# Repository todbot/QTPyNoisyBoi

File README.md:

# QTPyNoisyBoi

## QTPy/XIAO-based noisy 3-channel CV modulator Eurorack synth module

This is a bad idea.

It has:
- 3 CV outputs
- 1 gate input
- 3 knobs (next to outputs)
- 3 Neopixels (next to outputs)
- 2 tap buttons
- 1 neopixel on QT Py

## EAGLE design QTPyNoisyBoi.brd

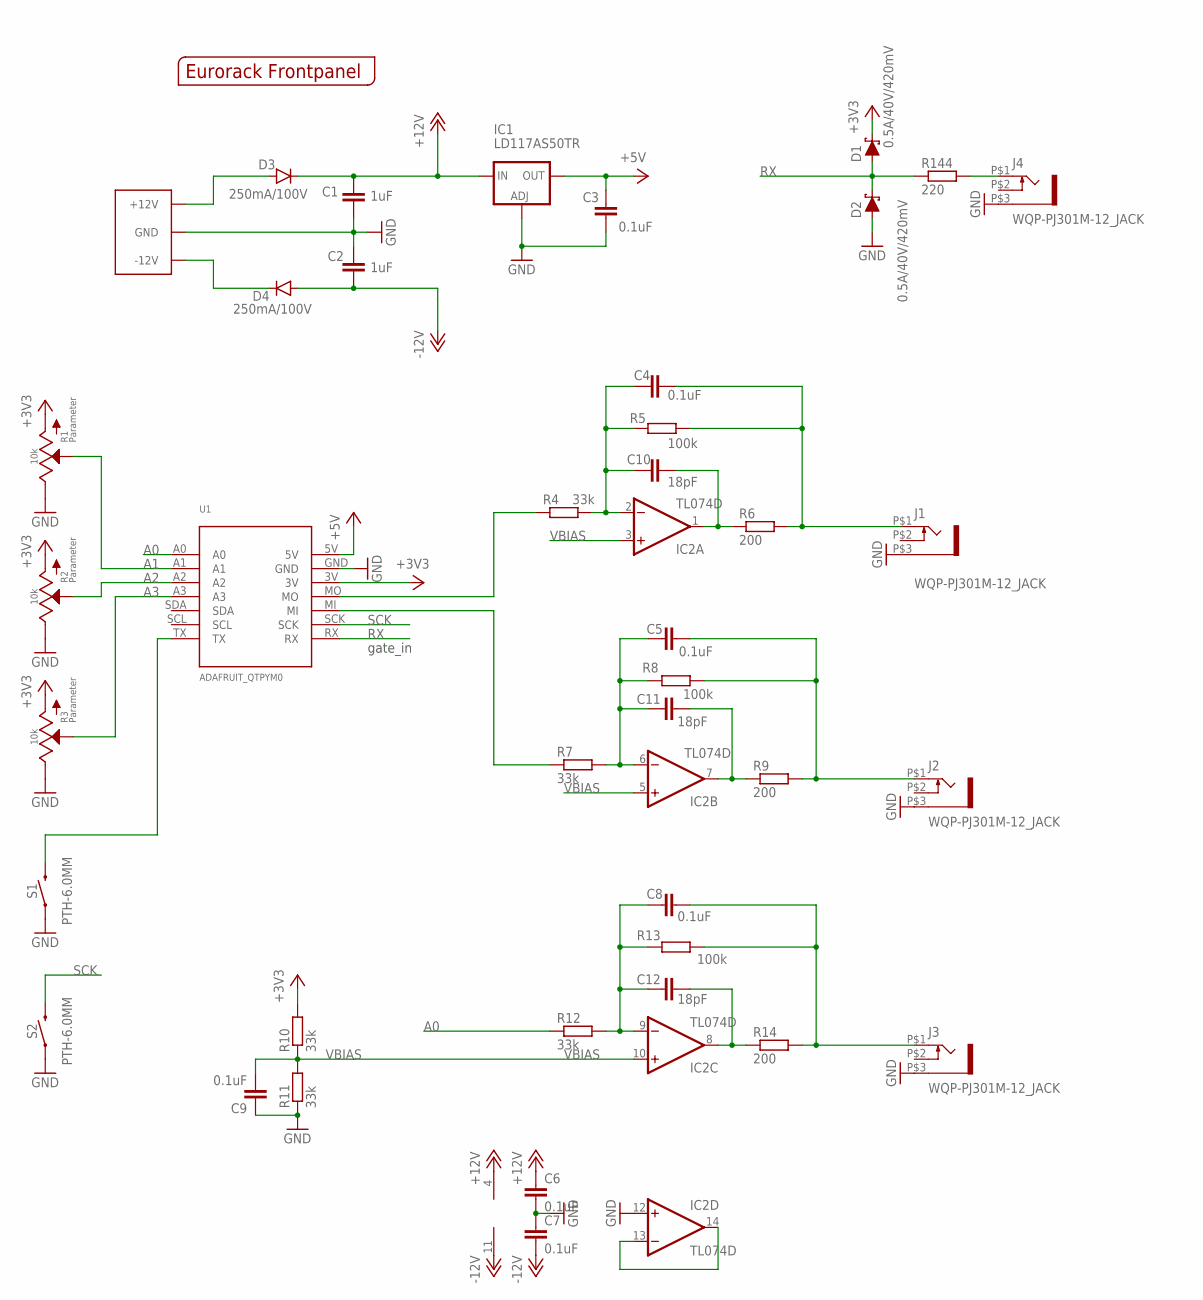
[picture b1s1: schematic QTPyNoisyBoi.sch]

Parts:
C1, C2: 1uF; C0805
C3, C4, C5, C6, C7, C8, C9: 0.1uF; C0805
C10, C11, C12: 18pF; C0805
D1, D2: 0.5A/40V/420mV; SOD-323
D3, D4: 250mA/100V; SOD-323
DIM1: EURO_POWER_LOCKSKINNY; EURO_POWER_HEADER
IC1: LD117AS50TR; SOT223
IC2: TL074D; SO14
J1, J2, J3, J4: WQP-PJ301M-12_JACK
R1, R2, R3: 10k; OG-POTS_ALPS_POT_VERTICAL
R4, R7, R10, R11, R12: 33k; R0805
R5, R8, R13: 100k; R0805
R6, R9, R14: 200; R0805
R144: 220; R0805
S1, S2: PTH-6.0MM; TACTILE_SWITCH_PTH_6.0MM
U1: ADAFRUIT_QTPYM0; ADAFRUIT_QTPY_M0
U$1: EURORACK_PANEL6HP; EURORACK6HPPANEL

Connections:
+3V3: D1.C, R1.P$3 (A), R2.P$3 (A), R3.P$3 (A), R10.2, U1.3V
+5V: C3.2, IC1.4 (OUT), U1.5V
+12V: C1.2, C6.1, D3.C, IC1.3 (IN), IC2.4 (V+)
-12V: C2.1, C7.2, D4.A, IC2.11 (V-)
A0: R12.1, U1.A0
A1: R1.P$2 (S), U1.A1
A2: R2.P$2 (S), U1.A2
A3: R3.P$2 (S), U1.A3
GND: C1.1, C2.2, C3.1, C6.2, C7.1, C9.1, D2.A, DIM1.3 (GND), DIM1.4 (GND), DIM1.5 (GND), DIM1.6 (GND), DIM1.7 (GND), DIM1.8 (GND), IC1.1 (ADJ), IC2.12 (+IN), J1.P$3 (1), J2.P$3 (1), J3.P$3 (1), J4.P$3 (1), R1.P$1 (E), R2.P$1 (E), R3.P$1 (E), R11.1, S1.1, S2.1, U1.GND
unnamed: C5.2, J2.P$1 (2), R8.2, R9.2
unnamed: S1.3 (2), U1.TX
unnamed: C12.2, IC2.8 (OUT), R14.1
unnamed: C8.1, C12.1, IC2.9 (-IN), R12.2, R13.1
unnamed: J4.P$1 (2), R144.2
unnamed: R4.1, U1.MO
unnamed: R7.1, U1.MI
unnamed: IC2.13 (-IN), IC2.14 (OUT)
unnamed: C4.2, J1.P$1 (2), R5.2, R6.2
unnamed: C4.1, C10.1, IC2.2 (-IN), R4.2, R5.1
unnamed: C8.2, J3.P$1 (2), R13.2, R14.2
unnamed: D4.C, DIM1.1 (-12V), DIM1.2 (-12V)
unnamed: C5.1, C11.1, IC2.6 (-IN), R7.2, R8.1
unnamed: C11.2, IC2.7 (OUT), R9.1
unnamed: D3.A, DIM1.9 (+12V), DIM1.10 (+12V)
unnamed: C10.2, IC2.1 (OUT), R6.1
RX: D1.A, D2.C, R144.1, U1.RX
SCK: S2.3 (2), U1.SCK
VBIAS: C9.2, IC2.3 (+IN), IC2.5 (+IN), IC2.10 (+IN), R10.1, R11.2

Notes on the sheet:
gate_in

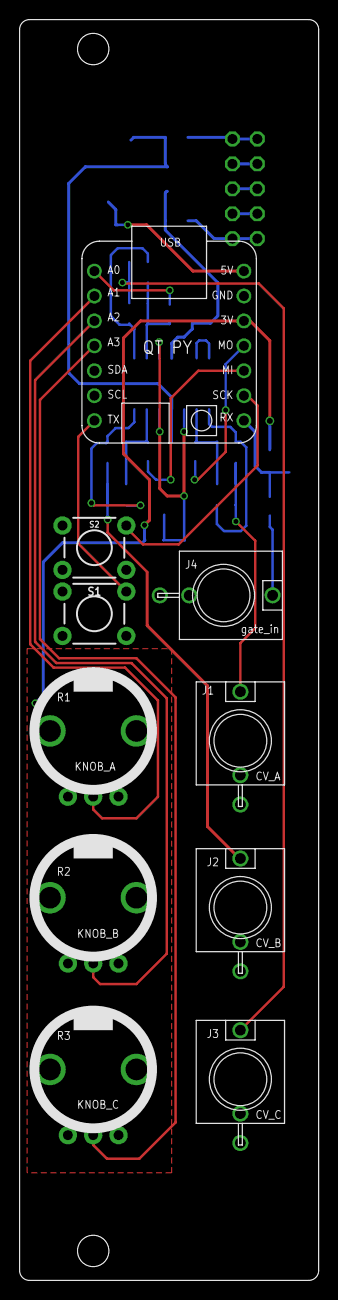
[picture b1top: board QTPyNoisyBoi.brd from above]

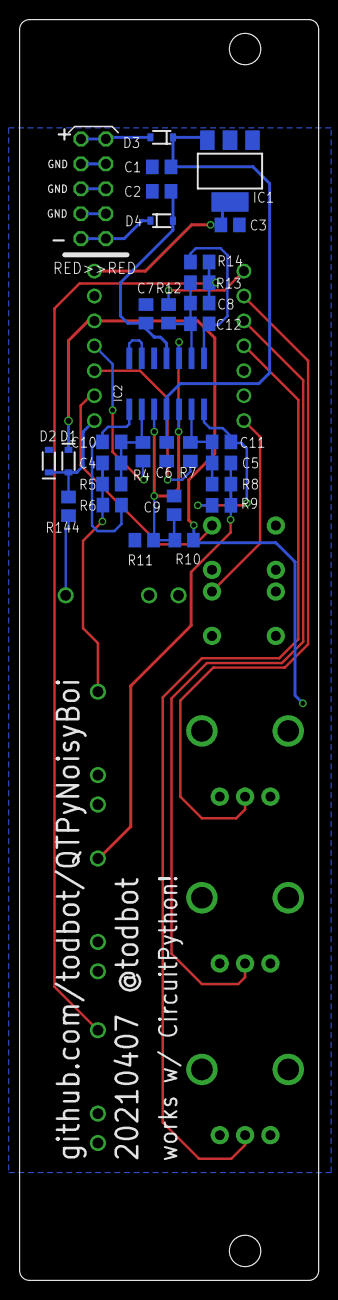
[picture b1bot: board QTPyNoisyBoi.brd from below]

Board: 2 copper layers, 30.5 x 128.5 mm, 42 parts (31 on the bottom side), 28 nets.

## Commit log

2021-03-24 added cap on vmidref; various cleanup
2021-03-31 sigh
2021-04-01 submit to fab
2021-04-08 fix dumb +/- opamp input swap on B and C
2021-04-08 added 2nd button
2021-04-10 added neopixels, woorah
2021-04-12 some progress
2021-04-18 cleanup silkscreen
2021-04-28 moving to Arduino because CircuitPython has poor timing accuracy (but lovely PWM)
2021-04-28 added first cut at the calibration stuff
2021-04-29 more Arduino-way progress
2021-04-29 feature list in readme
2021-09-07 added PTH idea

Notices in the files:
parts and their libraries:
SparkFun-DiscreteSemi: Licensing: Creative Commons ShareAlike 4.0 International - https://creativecommons.org/licenses/by-sa/4.0
